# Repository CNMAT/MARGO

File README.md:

# CNMAT MARGO: An ESP32-based gesture control platform with OSC

This is an example project that implements an affordable gesture control platform using an ESP32 and Inertial Measurement Unit (IMU) with Magnetometer connected over I2C.  The examples in this project illustrate ways to set up wireless networking functionality on the ESP32, how to access sensor data on connected I2C devices, how to process that data and transmit it to a network client as an OSC bundle.  The MARGO.ino file allows the end user to set up the ESP32 as a named wireless access point.  After connecting to this AP and transmitting any message to it via broadcast UDP, the MARGO will automatically begin sending its data stream to the IP address from which the request was initiated.

The examples in this repo were developed with the LSM6DS3 + LIS3MDL magnetic, angular rate and gravity (MARG) sensor.  Popular versions of this sensor incorporate a thermometer, thereby offering 10 degrees of freedom.  Sensor integration is accomplished via an implementation of Sebastian Madgwick's gradient descent orientation filter, which yeilds a stable quaternion orientation from which is derived the orientation in Euler angles.  Raw values of the sensor data, as well as the quaternion and Euler angles are transmitted as the following OSC bundle:

- /millis : {number of milliseconds since ESP32 boot}
- /Mag_XYZ : {magnetic vector in the sensor frame X,Y,Z (Gauss)} 
- /uTesla : {magnetic vector in sensor frame X,Y,Z (micro-Teslas)}
- /accel : {acceleration in sensor frame X,Y,Z (m/s^2)}
- /gyro : {sensor's angular rate of rotation around sensor's X, Y, Z (radians / second)
- /temp : {sensor's measured temperature (degrees C)
- /Madgwick : {unit quaternion describing rotation from sensor frame to Earth frame [q_1, q_2, q_3, q_4]}
- /Euler : {conversion of Madgwick quaternion to Euler angle representation (radians) [pitch, roll, yaw]

(ESP32 will print useful debugging data in the Arduino Serial Monitor console when connected to Arduino IDE at boot; see serial monitor for conversion factors of Magnetometer, accelerometer & gyro; )

The MARGO also accepts OSC messages for configuration on the fly:

- /setPort : {int port}  ---  sets destination port
- /setIP : {int[4] aaa, bbb, ccc, ddd}   --- sets destination IP
- /setLoopFreq : {int freq}   --- sets the refresh rate (how often the sensor is read) (Hertz)
- /calibrate : {null}  --- reset the orientation quaternion to [1,0,0,0] and re-initialize related parameters

# Getting Started
0. Obtain an ESP32 and a LSM6DS3 + LIS3MDL magnetic, angular rate and gravity (MARG) sensor.  See the [BOM.md](Hardware/BOM.md) for a complete listing of components.  You will also need:
    - The Arduino IDE
    - Max (available from Cycling74.com)
    - CNMAT's ODOT package (in Max, go to File > Show Package Manager > search odot, click on "odot" then install. Restart Max.)
1. Download this repo to your computer.  We recommend using GitHub desktop if you are uncomfortable with git.
    - Be sure to occasionally fetch changes to keep up with latest updates.
2. Connect the LSM6DS3 + LIS3MDL sensor to the ESP32 (see also [Connections](Hardware/Connections.md)):
    - Connect 3V3 pin on sensor to 3V3 pin on ESP32
    - Connect GND pin on sensor to GND pin on ESP32
    - Connect CLK pin on sensor to CLK pin (pin 22) on ESP32
    - Connect SDA pin on sensor to SDA pin (pin 21) on ESP32
3. Open the Arduino IDE
    - Be sure to install your ESP variant in the Tools>Board>Boards Manager (we used the ESP32-Devkitc-V4, which works with the ESP32-WROOM-DA Module profile)
4. Open the MARGO.ino file.
    - Change the ssid in the code to a name you wish to use. This will becoome the name of the wireless network set up by the MARGO. 
    - Make any desired customizations.
    - Connect ESP32 to computer with micro-USB cable.
    - Assign the correct port in Tools>Port> ... (the correct port will look something like "/dev/cu.usbserial-xxxx")
    - Upload the sketch to the ESP32 (click upload arrow in Arduino IDE window (or shift-command-R on Mac)
    - (ESP32 code takes a minute to compile and upload, be patient).
    - Switch to Serial Monitor in the Arduino IDE; Reboot the ESP32 by pressing either of its buttons.  If everything is working, you should see something like the following in the Serial Monitor:
    ```
    Setting AP (Access Point)…AP IP address: 192.168.4.1
    UDP listening on port: 1750
    LSM6DS3TR-C Found!
    Accelerometer range set to: +-4G
    Gyro range set to: 2000 degrees/s
    Accelerometer data rate set to: 104 Hz
    Gyro data rate set to: 104 Hz
    LIS3MDL Found!
    Performance mode set to: Medium
    Operation mode set to: Continuous
    Data rate set to: 155 Hz
    Range set to: +-4 gauss
    ```
4. Once the ESP32 is powered and running, it should appear as a wireless network (We named ours CNMAT-MARGO-1). Your credentials are those defined in the MARGO.ino as password (we used '123456789').
    
5. Open the 00_MARGO_START_HERE.maxpat
  - By default, the MARGO sketch will begin sending OSC packets to the IP address of the last message it recieved, so we just need to send it a packet--any packet--to get it sending sensor values to our Max patch.

In our early tests, the MARGO_AP configuration was able to run between 4-8 hours on a single charge of the 1200 mAh LiPoly battery.  Your results may vary depending on choice of battery and loop frequency.

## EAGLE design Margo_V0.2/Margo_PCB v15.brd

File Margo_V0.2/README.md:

The files in this directory were created in Autodesk Fusion 360. They describe a daughter board for an ESP-32-Devkit-C that securely and reliably mount peripherals for the MARGO implementation.  This prototype, tentatively called MARGO 0.2, is an attempt to miniaturize the footprint of the MARGO into a solid-stated device of 1" x 2" in size.

Margo v0.2 Board

Mounted to ESP32-DevKit-C, charging cable attached

# Features
* LSM6DSOTRLGA and LIS3DHTRL sensors for Magnetometer, Acceleration, Rotation & Gyroscope Sensors. These have been upgraded due to supply chain concerns but do require slightly different addressing to run.
* incorporates a power switch and on-board battery charger.

# TO DO
* Include a voltage divider to monitor battery charge via ADC pins.
* Consolidate onto single board with ESP32-WROOM-32U
* Relocate battery connector
* Consider flipping board for back-to-back mounting.
* Need to Improve Magnetometer Calibration for Hard and Soft Iron distortion.

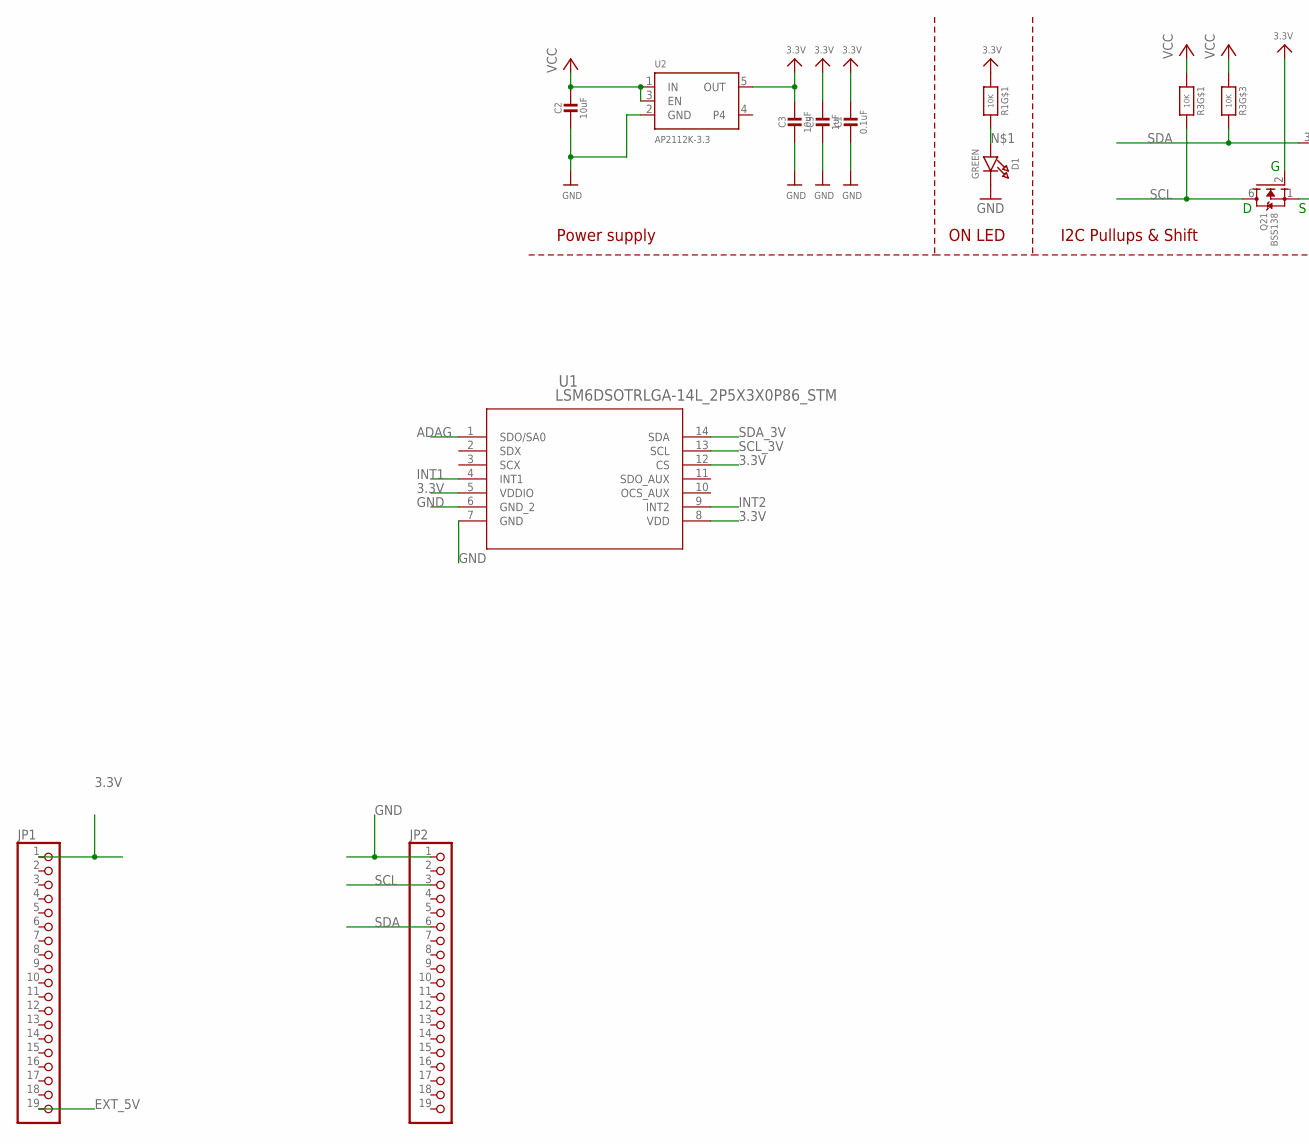
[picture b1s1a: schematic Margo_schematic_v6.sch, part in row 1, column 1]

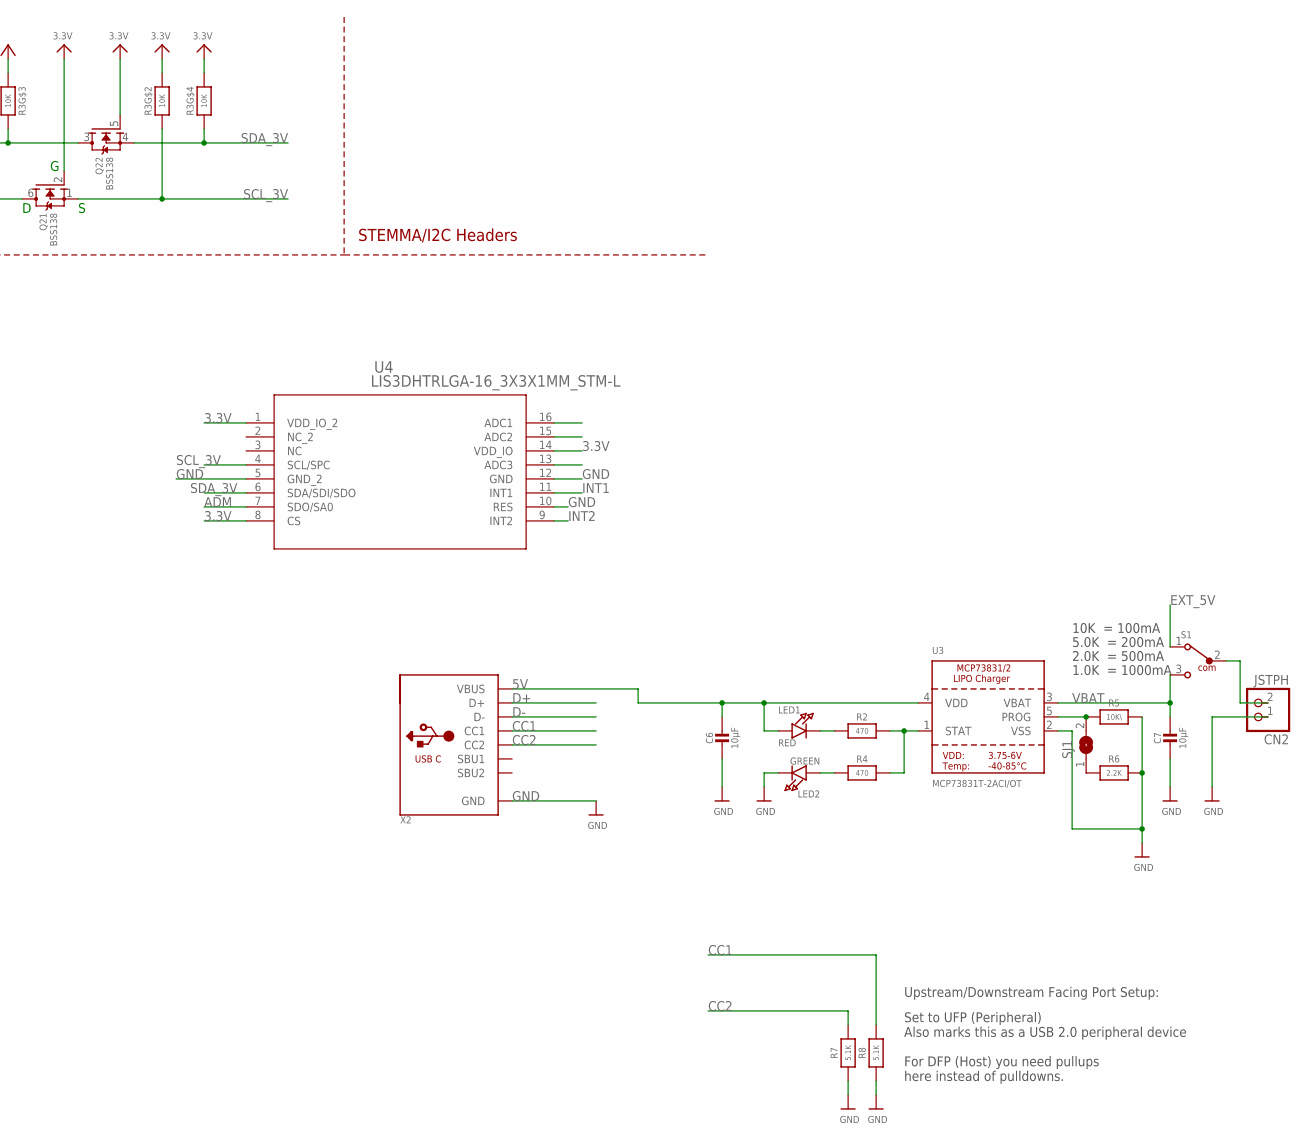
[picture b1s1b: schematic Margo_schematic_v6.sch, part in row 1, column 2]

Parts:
C1: 0.1uF; 0603-NO@1
C2, C3: 10uF; 0805-NO@1
C5: 1uF; 0603-NO@1
C6, C7: 10µF; 0805-NO@1
CN2: JSTPH; JSTPH2
D1: GREEN; CHIPLED_0603_NOOUTLINE
JP1, JP2: PINHD-1X19; 1X19
LED1: RED; CHIPLED_0805_NOOUTLINE
LED2: GREEN; CHIPLED_0805_NOOUTLINE
Q2: BSS138; SOT363
R1, R3: 10K; RESPACK_4X0603
R2, R4: 470; 0603-NO
R5: 10K\; 0603-NO
R6: 2.2K; 0603-NO
R7, R8: 5.1K; 0603-NO
S1: 450404015514
SJ1: SOLDERJUMPER; SOLDERJUMPER_ARROW_NOPASTE
U1: LSM6DSOTRLGA-14L_2P5X3X0P86_STM; LGA-14L_2P5X3X0P86_STM
U2: AP2112K-3.3; SOT23-5
U3: MCP73831T-2ACI/OT; SOT23-5
U4: LIS3DHTRLGA-16_3X3X1MM_STM-L; LGA-16_3X3X1MM_STM-L
X2: USB_C; USB_C_CUSB31-CFM2AX-01-X

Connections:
3.3V: C1.1, C3.1, C5.1, JP1.1, Q2.2 (G), Q2.5 (G), R1.1, R3.2 (1), R3.4 (1), U1.5 (VDDIO), U1.8 (VDD), U1.12 (CS), U2.5 (OUT), U4.1 (VDD_IO_2), U4.8 (CS), U4.14 (VDD_IO)
5V: C6.1, LED1.A, U3.4 (VDD), X2.A4B9 (VBUS), X2.B4A9 (VBUS)
ADAG: U1.1 (SDO/SA0)
ADM: U4.7 (SDO/SA0)
CC1: R8.2, X2.A5 (CC1)
CC2: R7.2, X2.B5 (CC2)
D+: X2.A6 (D+), X2.B6 (D+)
D-: X2.A7 (D-), X2.B7 (D-)
EXT_5V: JP1.19, S1.1
GND: C1.2, C2.2, C3.2, C5.2, C6.2, C7.2, CN2.1, D1.C, JP2.1, LED2.C, R5.2, R6.2, R7.1, R8.1, U1.6 (GND_2), U1.7 (GND), U2.2 (GND), U3.2 (VSS), U4.5 (GND_2), U4.10 (RES), U4.12 (GND), X2.A1B12 (GND), X2.B1A12 (GND)
INT1: U1.4 (INT1), U4.11 (INT1)
INT2: U1.9 (INT2), U4.9 (INT2)
unnamed: D1.A, R1.8 (2)
unnamed: LED1.C, R2.1
unnamed: R2.2, R4.2, U3.1 (STAT)
unnamed: R6.1, SJ1.1
unnamed: R5.1, SJ1.2, U3.5 (PROG)
unnamed: LED2.A, R4.1
unnamed: CN2.2, S1.2
SCL: JP2.3, Q2.6 (D), R3.8 (2)
SCL_3V: Q2.1 (S), R3.7 (2), U1.13 (SCL), U4.4 (SCL/SPC)
SDA: JP2.6, Q2.3 (D), R3.6 (2)
SDA_3V: Q2.4 (S), R3.5 (2), U1.14 (SDA), U4.6 (SDA/SDI/SDO)
VBAT: C7.1, S1.3, U3.3 (VBAT)
VCC: C2.1, R3.1, R3.3 (1), U2.1 (IN), U2.3 (EN)

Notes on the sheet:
I2C Pullups & Shift
STEMMA/I2C Headers
ON LED
Power supply
10K = 100mA
5.0K = 200mA
2.0K = 500mA
1.0K = 1000mA
Set to UFP (Peripheral) Also marks this as a USB 2.0 peripheral device For DFP (Host) you need pullups here instead of pulldowns.
Upstream/Downstream Facing Port Setup:

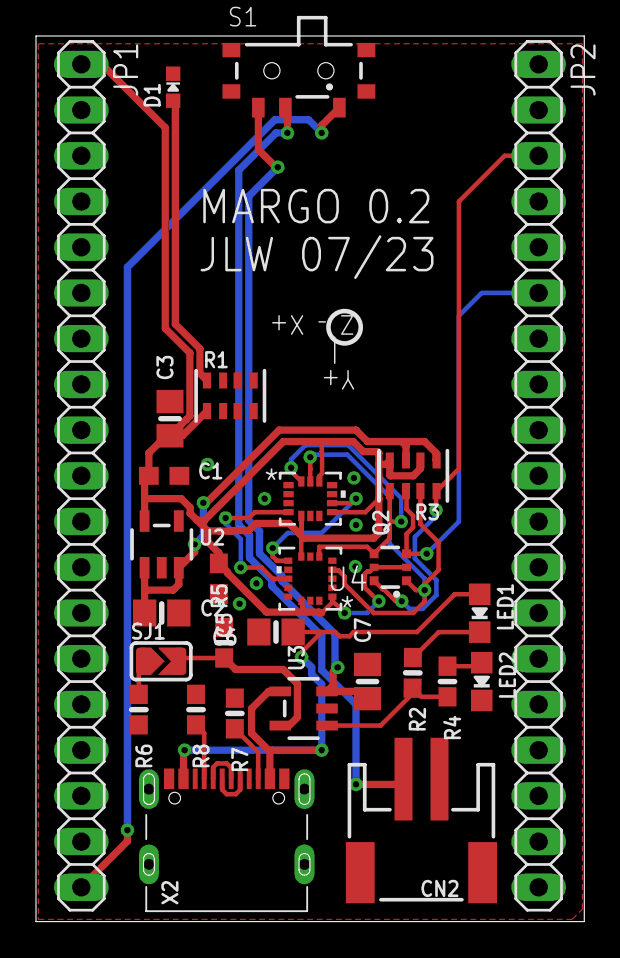
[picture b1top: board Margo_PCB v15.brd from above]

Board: 2 copper layers, 30.5 x 49.2 mm, 28 parts (0 on the bottom side), 23 nets.

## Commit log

2022-10-31 Cleaning Up to get ready for new variations
2023-07-11 Adding Schematic and Board for Margo Backpack
    Updating with Margo_v0.2 hardware designs and new Arduino Sketch that handles the slightly different sensors used in this prototype: LSM6DSOTRL & LIS3DHTRL.
2023-07-11 Collecting v0.2 resources
2023-07-11 Organizing max examples
2023-07-14 Update README.md
    adding TODO
2023-07-14 Updating Iron Losses Patch.
2023-12-08 Updates after OpenLab

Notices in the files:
parts and their libraries:
microbuilder: This work is placed in the public domain, and may be freely used for commercial and non-commercial work with the following conditions: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
Wurth_Switch_WS-SLSU: Copyright: Würth Elektronik
COPYRIGHT: Copyright (C) 2023 Ultra Librarian. All rights reserved.
